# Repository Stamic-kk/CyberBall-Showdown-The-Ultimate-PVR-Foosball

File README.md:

# CyberBall-Showdown-The-Ultimate-PVR-Foosball
Purdue ECE Senior Design. A Player vs. Robot foosball table consists of ball tracking, trajectory computation, and motion control. A Jetson Nano serves as the central computation core, and a STM32F091 MCU is charge of all measurements and motion controls. \
See our website for any progress: https://engineering.purdue.edu/477grp9/ 
##
## Description
### Project Name: *Cyberball: The Ultimate PVR Foosball*
Foosball has been a popular form of entertainment for people of all ages. However, one constraint of the game is that it needs two people to play. It is not entertainment for an individual. Based on this issue, “Cyberball: PVR Foosball table” enables a player to play against an automated system, which consists of a high speed camera, three arrays of digital hall-effect sensors, two dedicated MCUs, and a set of servo motors.
The STM32 MCU leverages the data collected from hall-effect sensors to determine the location of the players on the rods. It then sends the location data to the Jetson Nano Developer Kit via UART protocol. The high speed camera captures the images of the foosball table and sends them to the Nano developer kit by USB protocol and Gstreamer pipeline with v4l2. Nano Developer Kit runs the Min-Max Location algorithm from the vision programming interface(VPI) to locate the ball, predict the trajectory using the extended Kalman filter, and make the decisions on moving rods, which the MCU processes into motor control signals. To achieve the detection purpose, the ball is colored uniquely. A sensitive pressure sensor is used to detect the goals.
The dynamics of the system contain two dimensions. For the rotational aspect, each rod has a high torque servo motor attached. These motors are continuously signaled on a constant frequency PWM, which allows the figures on the rods to maintain a swaying, kicking motion. For lateral movement, a structure of cables and pulleys transfers the angular momentum generated by a high speed servo motor to the linear motion of the rod. An MCU generates the PWM signal that activates the transistor channels between the servo and the DC source to make the servo rotate to the desired angle. This angular displacement pulls the cable attached to the rod, moving it horizontally.
An OLED display and a keypad connected to the STM32 act as the user interface where the users start/reset the game and view their goals. The OLED display communicates with the MCU with the SPI protocol and can be used to display the scores and user command options. The keypad (button array) communicates with the MCU through GPIO to send commands including start (power-on), re-start, and pause.
The power constraints are summarized as follows. The system needs a 6.8V DC for all 6 servo motors. MCUs and Jetson Nano will be powered by a 3.6V DC and a 5V=4A supply, respectively. The total power consumption is estimated to be 120W. The user simply plugs in the supplied 12V 30A AC/DC adapter. A set of buck converters and linear regulators will step down the main power source to voltages/currents required by the components.
##
### File Organization
> CAD 
>> Fusion 3D file for packaging design. 

>CyberBall - Configuration Code deployed on STM32F091 MCU (via Software Peripheral)
>> inc - include headers\
>> src - source files\
>> CyberBallConfig.cfg - run/debug configuration

> PCB - Kicad PCB design files
>> Librarys - Customized PCB layouts\
>> Hall_effect_sensors - Rod Position measurement board (x3)\
>> Power_Supply - Power supply board (commerical regulator modules needed)\
>> Senior Design - Main function board \
>> User_Interface - User Interface board with a screen on it. 

> nanoBrain - central control system runing on Jetson Nano.
>> cppSolution - CMAKE project for the workflow running on Jetson Nano\
>>> include - include headers\
>>> src - source files\
>>> uKal - helper submodule for the Kalman filter\

## Notes
**IMPORTANT**: <font color="red"> The VDD and GND pin are reversed on the pinout of connection for servos on the power supply board.</font>
+ VDD labled on the board should connect to GND pin on the servo.
+ GND labled on the board should connect to VDD pin on the servo.
+ No changes should be made for PWM control signals.

Note: disabled nvgetty for uart

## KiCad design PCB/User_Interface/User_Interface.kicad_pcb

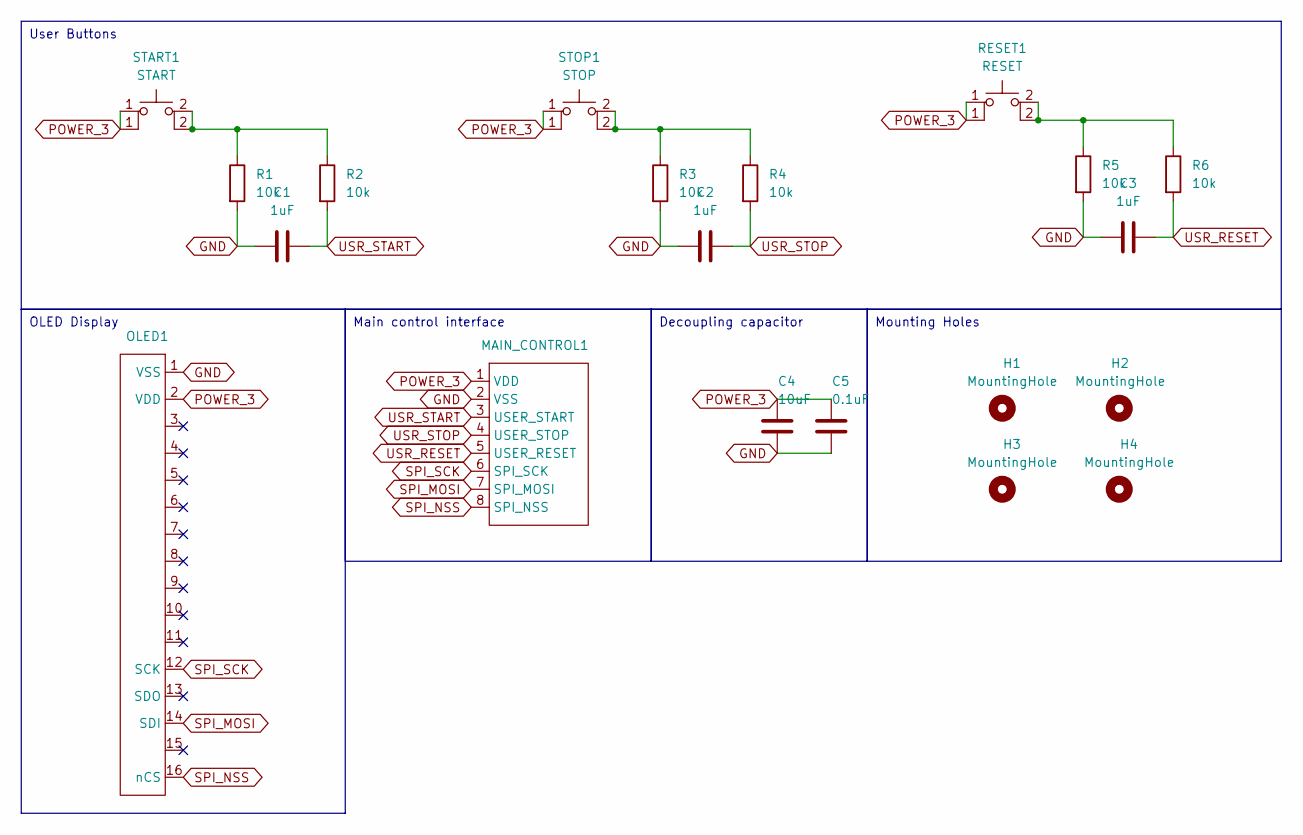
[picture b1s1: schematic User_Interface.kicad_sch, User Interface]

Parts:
C1, C2, C3: 1uF; C_1206_3216Metric_Pad1.33x1.80mm_HandSolder
C4: 10uF; C_1206_3216Metric_Pad1.33x1.80mm_HandSolder
C5: 0.1uF; C_1206_3216Metric_Pad1.33x1.80mm_HandSolder
H1, H2, H3, H4: MountingHole; MountingHole_4mm
MAIN_CONTROL1: PinSocket_1x08_P2.54mm_Vertical
OLED1: PinSocket_1x16_P2.54mm_Vertical
R1, R2, R3, R4, R5, R6: 10k; R_1206_3216Metric_Pad1.30x1.75mm_HandSolder
RESET1: RESET; SW_PUSH_6mm_H4.3mm
START1: START; SW_PUSH_6mm_H4.3mm
STOP1: STOP; SW_PUSH_6mm_H4.3mm

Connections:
GND: C1.1, C2.1, C3.1, C4.2, C5.2, MAIN_CONTROL1.2 (VSS), OLED1.1 (VSS), R1.2, R3.2, R5.2
unnamed: R5.1, R6.1, RESET1.2 (A)
unnamed: R1.1, R2.1, START1.2 (A)
unnamed: R3.1, R4.1, STOP1.2 (A)
POWER_3: C4.1, C5.1, MAIN_CONTROL1.1 (VDD), OLED1.2 (VDD), RESET1.1, START1.1, STOP1.1
SPI_MOSI: MAIN_CONTROL1.7 (SPI_MOSI), OLED1.14 (SDI)
SPI_NSS: MAIN_CONTROL1.8 (SPI_NSS), OLED1.16 (nCS)
SPI_SCK: MAIN_CONTROL1.6 (SPI_SCK), OLED1.12 (SCK)
USR_RESET: C3.2, MAIN_CONTROL1.5 (USER_RESET), R6.2
USR_START: C1.2, MAIN_CONTROL1.3 (USER_START), R2.2
USR_STOP: C2.2, MAIN_CONTROL1.4 (USER_STOP), R4.2

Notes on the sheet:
OLED Display
User Buttons
Main control interface
Decoupling capacitor
Mounting Holes

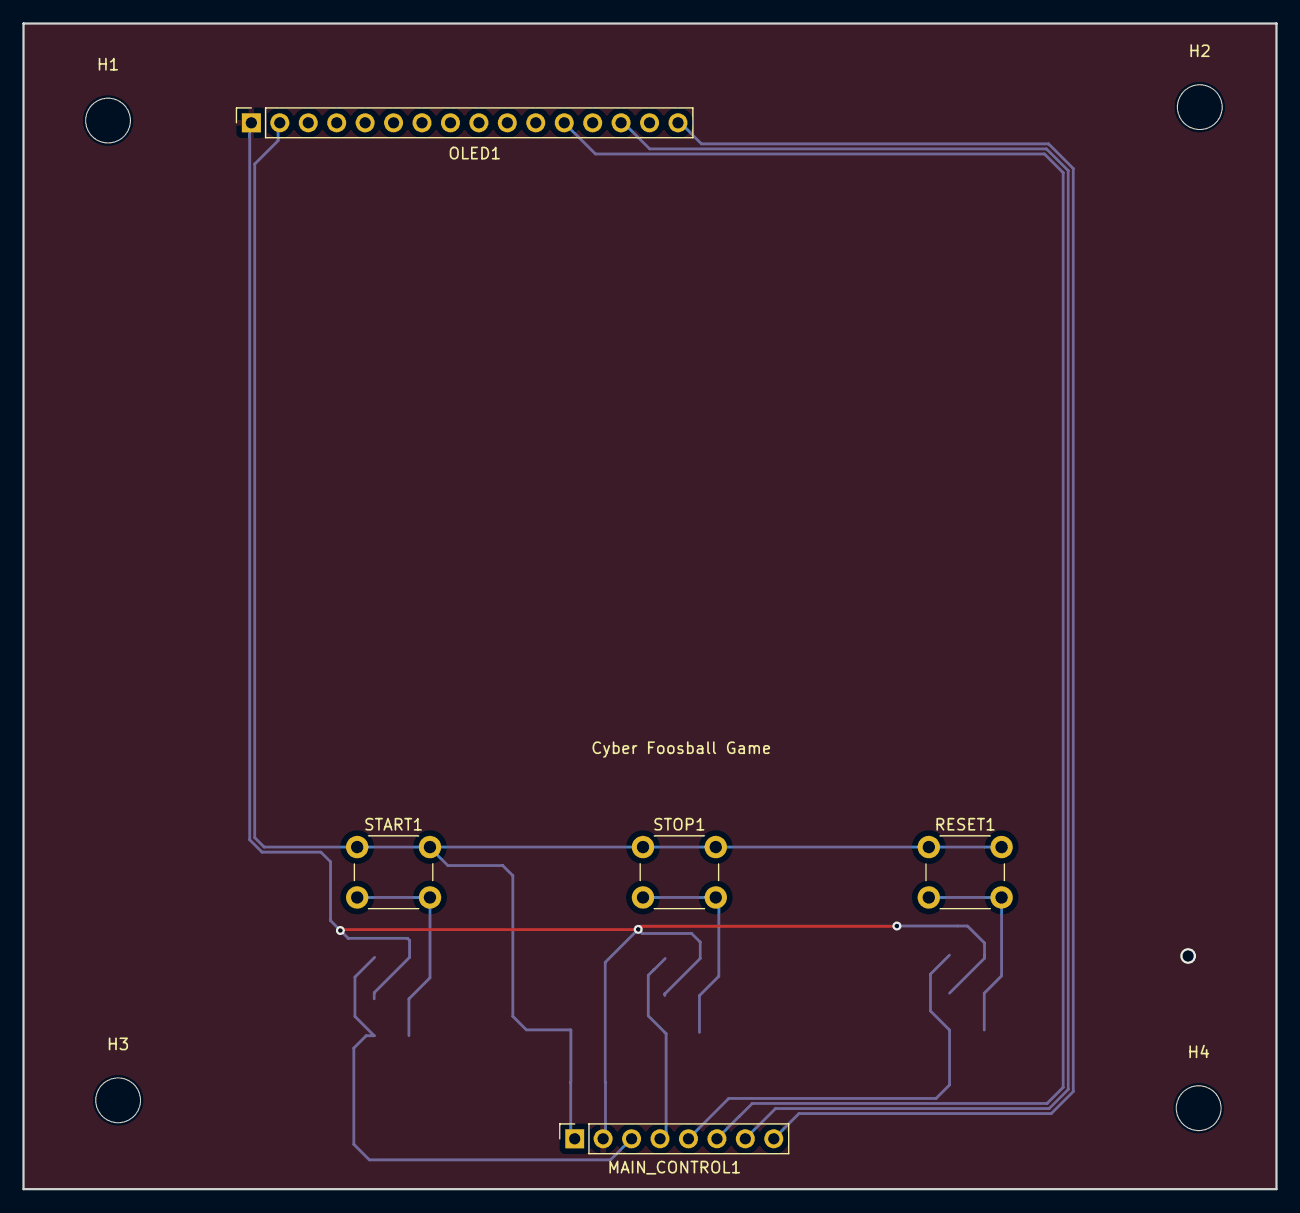
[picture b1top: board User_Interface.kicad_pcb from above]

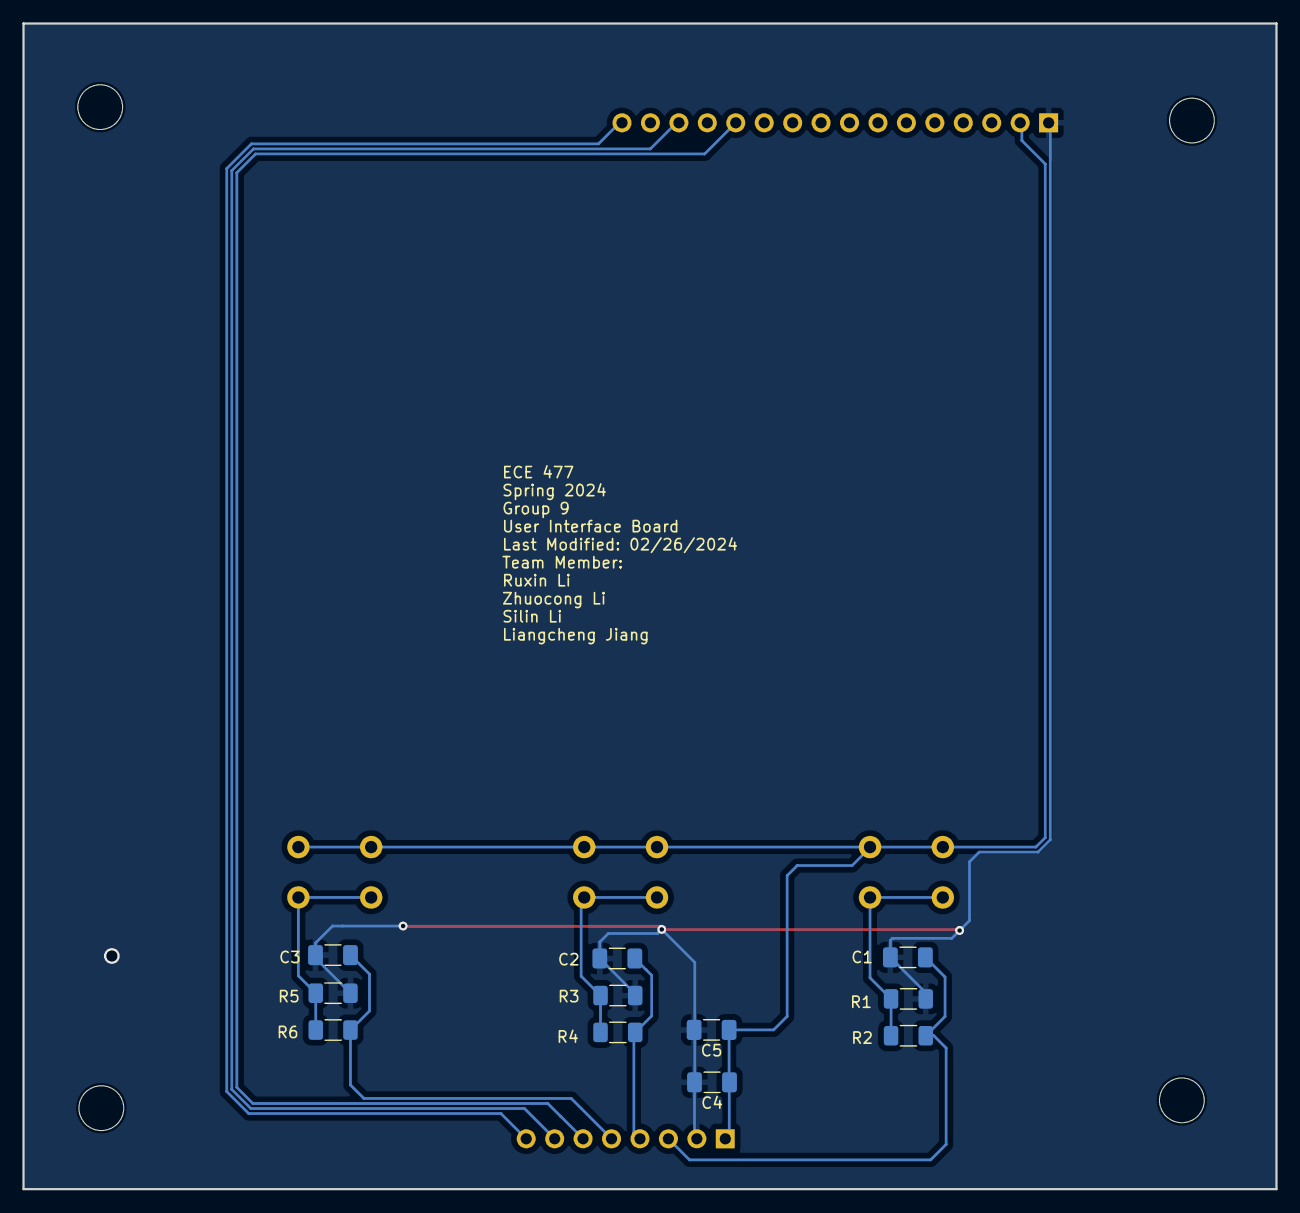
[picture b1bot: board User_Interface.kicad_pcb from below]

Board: 2 copper layers, 111.9 x 104.1 mm, 20 parts (11 on the bottom side), 11 nets.

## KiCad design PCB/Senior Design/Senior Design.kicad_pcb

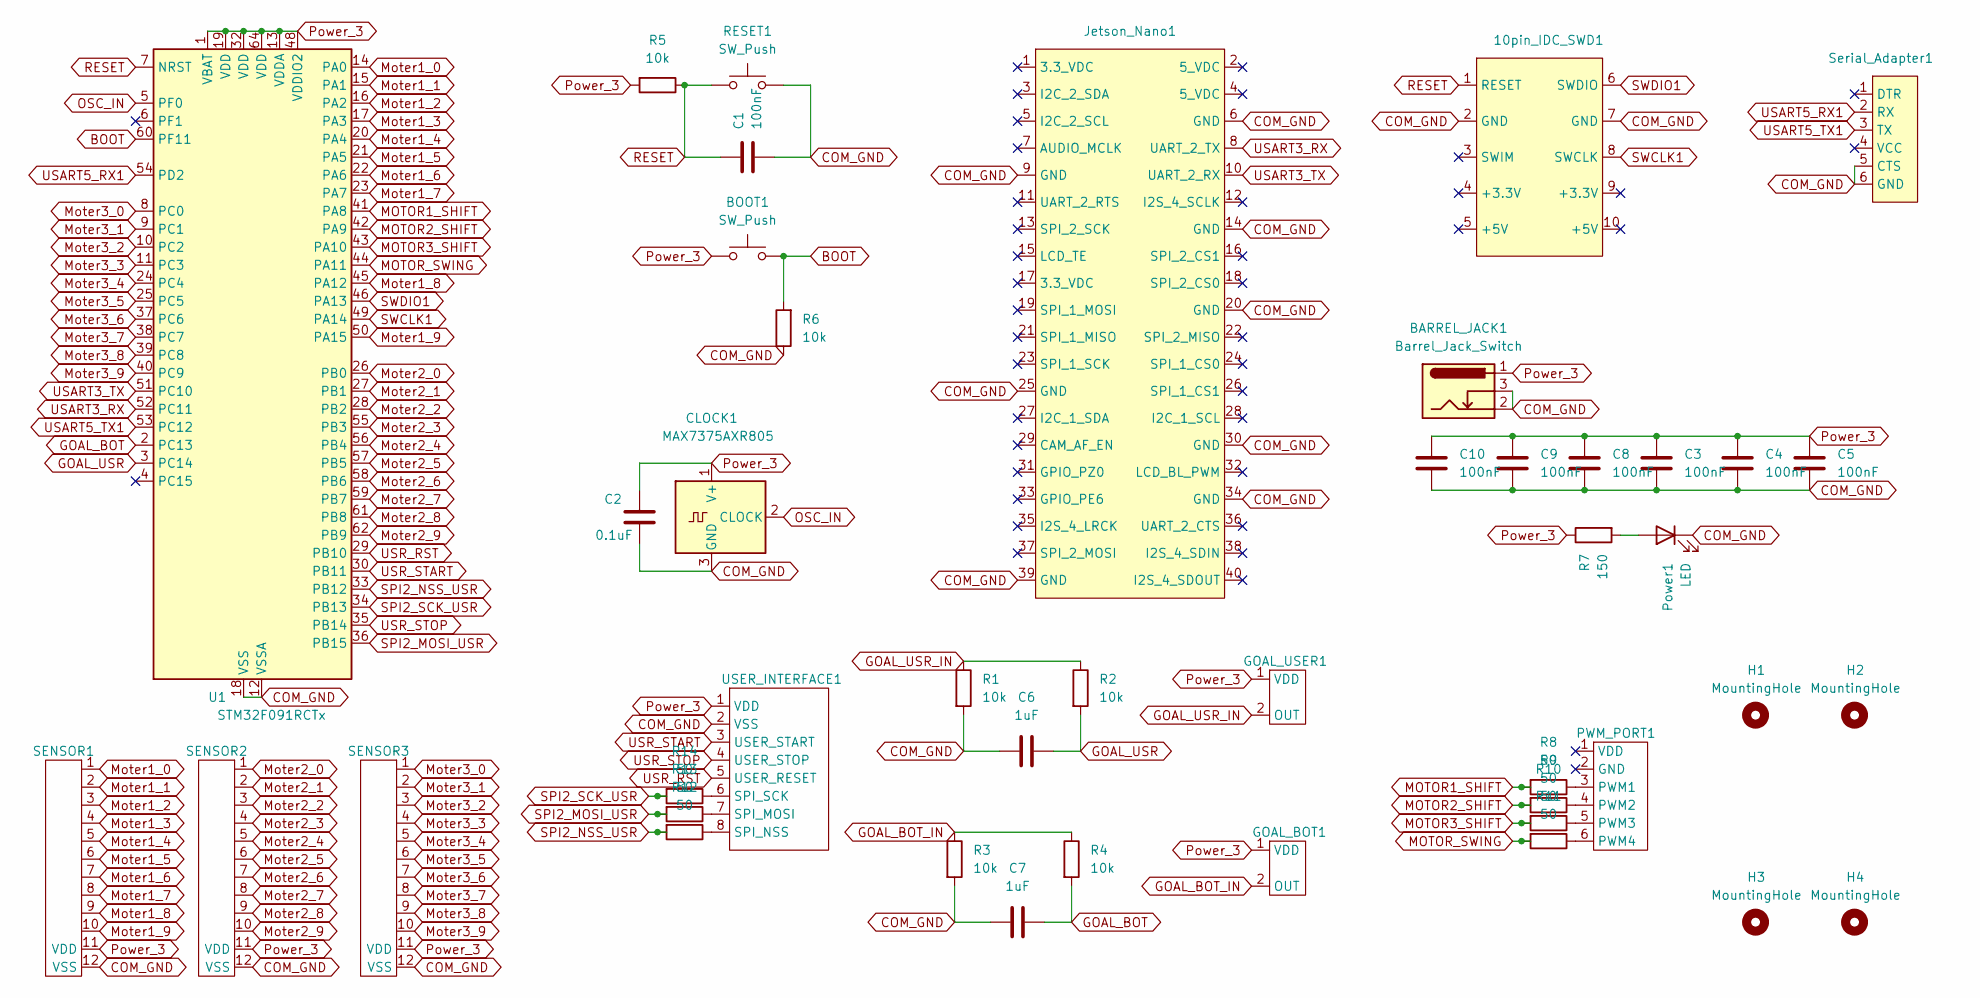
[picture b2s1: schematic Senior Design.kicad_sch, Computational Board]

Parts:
10pin_IDC_SWD1: IDC-Header_2x05_P2.54mm_Vertical_Modified
BARREL_JACK1: Barrel_Jack_Switch; BarrelJack_CUI_PJ-102AH_Horizontal
BOOT1: SW_Push; SW_PUSH_6mm_H4.3mm
C1, C3, C4, C5, C8, C9, C10: 100nF; C_1206_3216Metric_Pad1.33x1.80mm_HandSolder
C2: 0.1uF; C_1206_3216Metric_Pad1.33x1.80mm_HandSolder
C6, C7: 1uF; C_1206_3216Metric_Pad1.33x1.80mm_HandSolder
CLOCK1: MAX7375AXR805; SOT-323_SC-70
GOAL_BOT1: PinHeader_1x02_P2.54mm_Vertical
GOAL_USER1: PinHeader_1x02_P2.54mm_Vertical
H1, H2, H3, H4: MountingHole; MountingHole_4mm
Jetson_Nano1: PinHeader_2x20_P2.54mm_Vertical
PWM_PORT1: PinHeader_1x06_P2.54mm_Vertical
Power1: LED; LED_1206_3216Metric_Pad1.42x1.75mm_HandSolder
R1, R2, R3, R4, R5, R6: 10k; R_1206_3216Metric_Pad1.30x1.75mm_HandSolder
R7: 150; R_1206_3216Metric_Pad1.30x1.75mm_HandSolder
R8, R9, R10, R11, R12, R13, R14: 50; R_1206_3216Metric_Pad1.30x1.75mm_HandSolder
RESET1: SW_Push; SW_PUSH_6mm_H4.3mm
SENSOR1, SENSOR2, SENSOR3: PinHeader_1x12_P2.54mm_Vertical
Serial_Adapter1: PinSocket_1x06_P2.54mm_Vertical
U1: STM32F091RCTx; LQFP-64_10x10mm_P0.5mm
USER_INTERFACE1: PinHeader_1x08_P2.54mm_Vertical

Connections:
BOOT: BOOT1.2, R6.2, U1.60 (PF11)
COM_GND: 10pin_IDC_SWD1.2 (GND), 10pin_IDC_SWD1.7 (GND), BARREL_JACK1.2, BARREL_JACK1.3, C1.2, C2.2, C3.2, C4.2, C5.2, C6.1, C7.1, C8.2, C9.2, C10.2, CLOCK1.3 (GND), Jetson_Nano1.6 (GND), Jetson_Nano1.9 (GND), Jetson_Nano1.14 (GND), Jetson_Nano1.20 (GND), Jetson_Nano1.25 (GND), Jetson_Nano1.30 (GND), Jetson_Nano1.34 (GND), Jetson_Nano1.39 (GND), Power1.1 (K), R1.2, R3.2, R6.1, RESET1.2, SENSOR1.12 (VSS), SENSOR2.12 (VSS), SENSOR3.12 (VSS), Serial_Adapter1.5 (CTS), Serial_Adapter1.6 (GND), U1.12 (VSSA), U1.18 (VSS), U1.31 (VSS), U1.47 (VSS), U1.63 (VSS), USER_INTERFACE1.2 (VSS)
GOAL_BOT: C7.2, R4.2, U1.2 (PC13)
GOAL_BOT_IN: GOAL_BOT1.2 (OUT), R3.1, R4.1
GOAL_USR: C6.2, R2.2, U1.3 (PC14)
GOAL_USR_IN: GOAL_USER1.2 (OUT), R1.1, R2.1
MOTOR1_SHIFT: R8.2, U1.41 (PA8)
MOTOR2_SHIFT: R9.2, U1.42 (PA9)
MOTOR3_SHIFT: R10.2, U1.43 (PA10)
MOTOR_SWING: R11.2, U1.44 (PA11)
Moter1_0: SENSOR1.1, U1.14 (PA0)
Moter1_1: SENSOR1.2, U1.15 (PA1)
Moter1_2: SENSOR1.3, U1.16 (PA2)
Moter1_3: SENSOR1.4, U1.17 (PA3)
Moter1_4: SENSOR1.5, U1.20 (PA4)
Moter1_5: SENSOR1.6, U1.21 (PA5)
Moter1_6: SENSOR1.7, U1.22 (PA6)
Moter1_7: SENSOR1.8, U1.23 (PA7)
Moter1_8: SENSOR1.9, U1.45 (PA12)
Moter1_9: SENSOR1.10, U1.50 (PA15)
Moter2_0: SENSOR2.1, U1.26 (PB0)
Moter2_1: SENSOR2.2, U1.27 (PB1)
Moter2_2: SENSOR2.3, U1.28 (PB2)
Moter2_3: SENSOR2.4, U1.55 (PB3)
Moter2_4: SENSOR2.5, U1.56 (PB4)
Moter2_5: SENSOR2.6, U1.57 (PB5)
Moter2_6: SENSOR2.7, U1.58 (PB6)
Moter2_7: SENSOR2.8, U1.59 (PB7)
Moter2_8: SENSOR2.9, U1.61 (PB8)
Moter2_9: SENSOR2.10, U1.62 (PB9)
Moter3_0: SENSOR3.1, U1.8 (PC0)
Moter3_1: SENSOR3.2, U1.9 (PC1)
Moter3_2: SENSOR3.3, U1.10 (PC2)
Moter3_3: SENSOR3.4, U1.11 (PC3)
Moter3_4: SENSOR3.5, U1.24 (PC4)
Moter3_5: SENSOR3.6, U1.25 (PC5)
Moter3_6: SENSOR3.7, U1.37 (PC6)
Moter3_7: SENSOR3.8, U1.38 (PC7)
Moter3_8: SENSOR3.9, U1.39 (PC8)
Moter3_9: SENSOR3.10, U1.40 (PC9)
unnamed: PWM_PORT1.3 (PWM1), R8.1
unnamed: PWM_PORT1.4 (PWM2), R9.1
unnamed: PWM_PORT1.5 (PWM3), R10.1
unnamed: PWM_PORT1.6 (PWM4), R11.1
unnamed: Power1.2 (A), R7.2
unnamed: R13.1, USER_INTERFACE1.7 (SPI_MOSI)
unnamed: R12.1, USER_INTERFACE1.8 (SPI_NSS)
unnamed: R14.1, USER_INTERFACE1.6 (SPI_SCK)
OSC_IN: CLOCK1.2 (CLOCK), U1.5 (PF0)
Power_3: BARREL_JACK1.1, BOOT1.1, C2.1, C3.1, C4.1, C5.1, C8.1, C9.1, C10.1, CLOCK1.1 (V+), GOAL_BOT1.1 (VDD), GOAL_USER1.1 (VDD), R5.2, R7.1, SENSOR1.11 (VDD), SENSOR2.11 (VDD), SENSOR3.11 (VDD), U1.1 (VBAT), U1.13 (VDDA), U1.19 (VDD), U1.32 (VDD), U1.48 (VDDIO2), U1.64 (VDD), USER_INTERFACE1.1 (VDD)
RESET: 10pin_IDC_SWD1.1 (RESET), C1.1, R5.1, RESET1.1, U1.7 (NRST)
SPI2_MOSI_USR: R13.2, U1.36 (PB15)
SPI2_NSS_USR: R12.2, U1.33 (PB12)
SPI2_SCK_USR: R14.2, U1.34 (PB13)
SWCLK1: 10pin_IDC_SWD1.8 (SWCLK), U1.49 (PA14)
SWDIO1: 10pin_IDC_SWD1.6 (SWDIO), U1.46 (PA13)
USART3_RX: Jetson_Nano1.8 (UART_2_TX), U1.52 (PC11)
USART3_TX: Jetson_Nano1.10 (UART_2_RX), U1.51 (PC10)
USART5_RX1: Serial_Adapter1.2 (RX), U1.54 (PD2)
USART5_TX1: Serial_Adapter1.3 (TX), U1.53 (PC12)
USR_RST: U1.29 (PB10), USER_INTERFACE1.5 (USER_RESET)
USR_START: U1.30 (PB11), USER_INTERFACE1.3 (USER_START)
USR_STOP: U1.35 (PB14), USER_INTERFACE1.4 (USER_STOP)

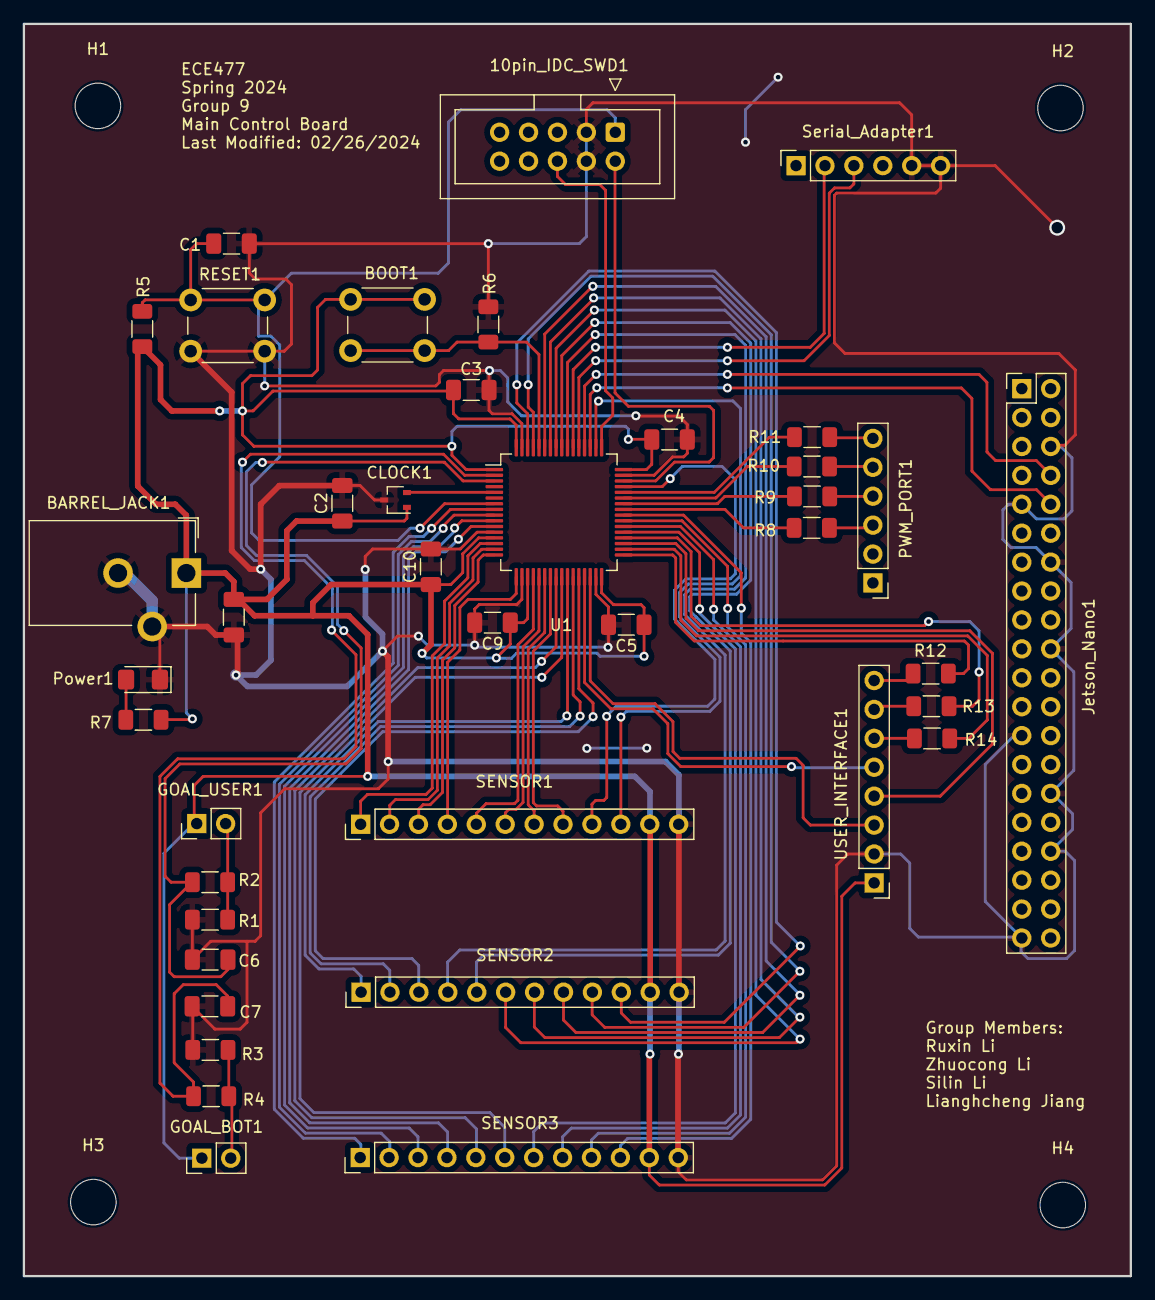
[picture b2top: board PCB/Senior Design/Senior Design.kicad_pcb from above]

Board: 2 copper layers, 97.2 x 110.0 mm, 44 parts (0 on the bottom side), 63 nets.

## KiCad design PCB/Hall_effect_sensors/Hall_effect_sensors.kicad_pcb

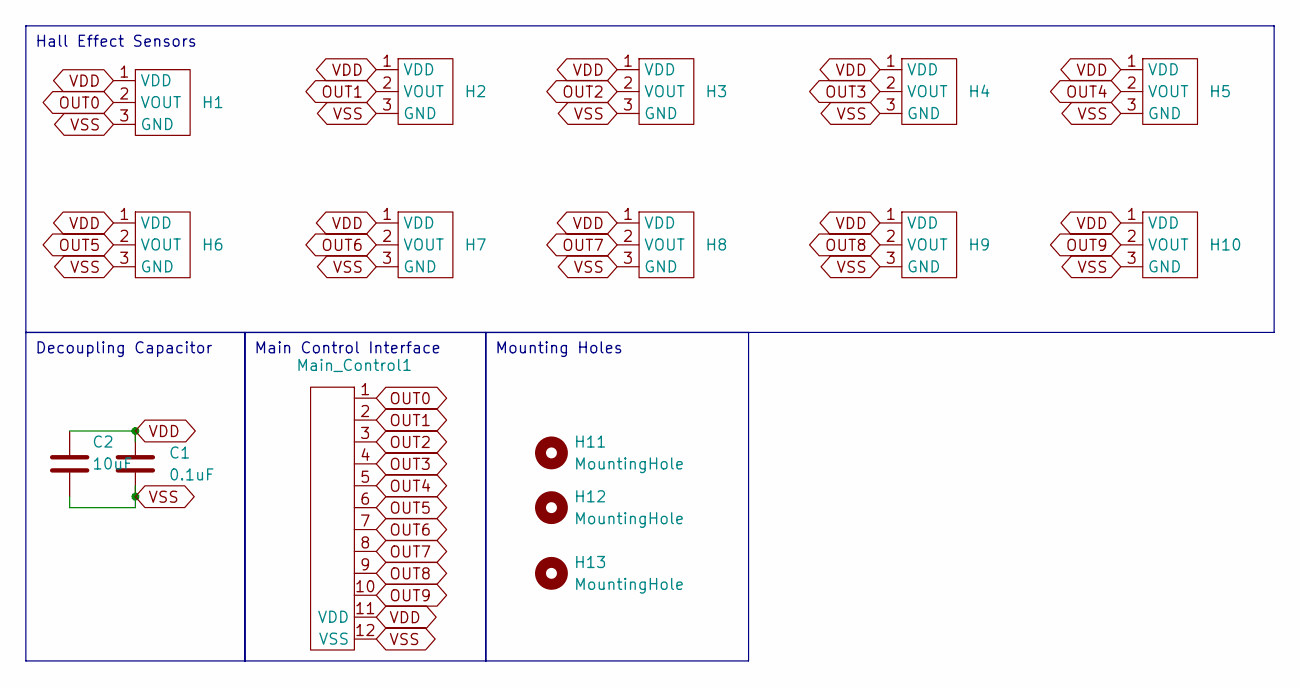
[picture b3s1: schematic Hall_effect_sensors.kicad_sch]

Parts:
C1: 0.1uF; C_1206_3216Metric_Pad1.33x1.80mm_HandSolder
C2: 10uF; C_1206_3216Metric_Pad1.33x1.80mm_HandSolder
H1, H2, H3, H4, H5, H6, H7, H8, H9, H10: SOT-23-3
H11, H12: MountingHole; MountingHole_4mm
H13: MountingHole; MountingHole_2mm
Main_Control1: Sensor Port

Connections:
OUT0: H1.2 (VOUT), Main_Control1.1
OUT1: H2.2 (VOUT), Main_Control1.2
OUT2: H3.2 (VOUT), Main_Control1.3
OUT3: H4.2 (VOUT), Main_Control1.4
OUT4: H5.2 (VOUT), Main_Control1.5
OUT5: H6.2 (VOUT), Main_Control1.6
OUT6: H7.2 (VOUT), Main_Control1.7
OUT7: H8.2 (VOUT), Main_Control1.8
OUT8: H9.2 (VOUT), Main_Control1.9
OUT9: H10.2 (VOUT), Main_Control1.10
VDD: C1.1, C2.1, H1.1 (VDD), H2.1 (VDD), H3.1 (VDD), H4.1 (VDD), H5.1 (VDD), H6.1 (VDD), H7.1 (VDD), H8.1 (VDD), H9.1 (VDD), H10.1 (VDD), Main_Control1.11 (VDD)
VSS: C1.2, C2.2, H1.3 (GND), H2.3 (GND), H3.3 (GND), H4.3 (GND), H5.3 (GND), H6.3 (GND), H7.3 (GND), H8.3 (GND), H9.3 (GND), H10.3 (GND), Main_Control1.12 (VSS)

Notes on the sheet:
Mounting Holes
Hall Effect Sensors
Main Control Interface
Decoupling Capacitor

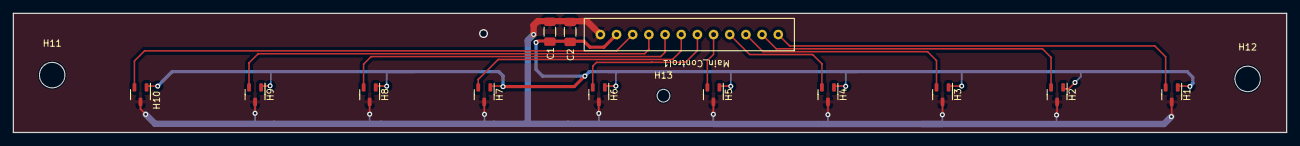
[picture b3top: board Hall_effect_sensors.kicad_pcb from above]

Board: 2 copper layers, 200.0 x 18.7 mm, 16 parts (0 on the bottom side), 12 nets.

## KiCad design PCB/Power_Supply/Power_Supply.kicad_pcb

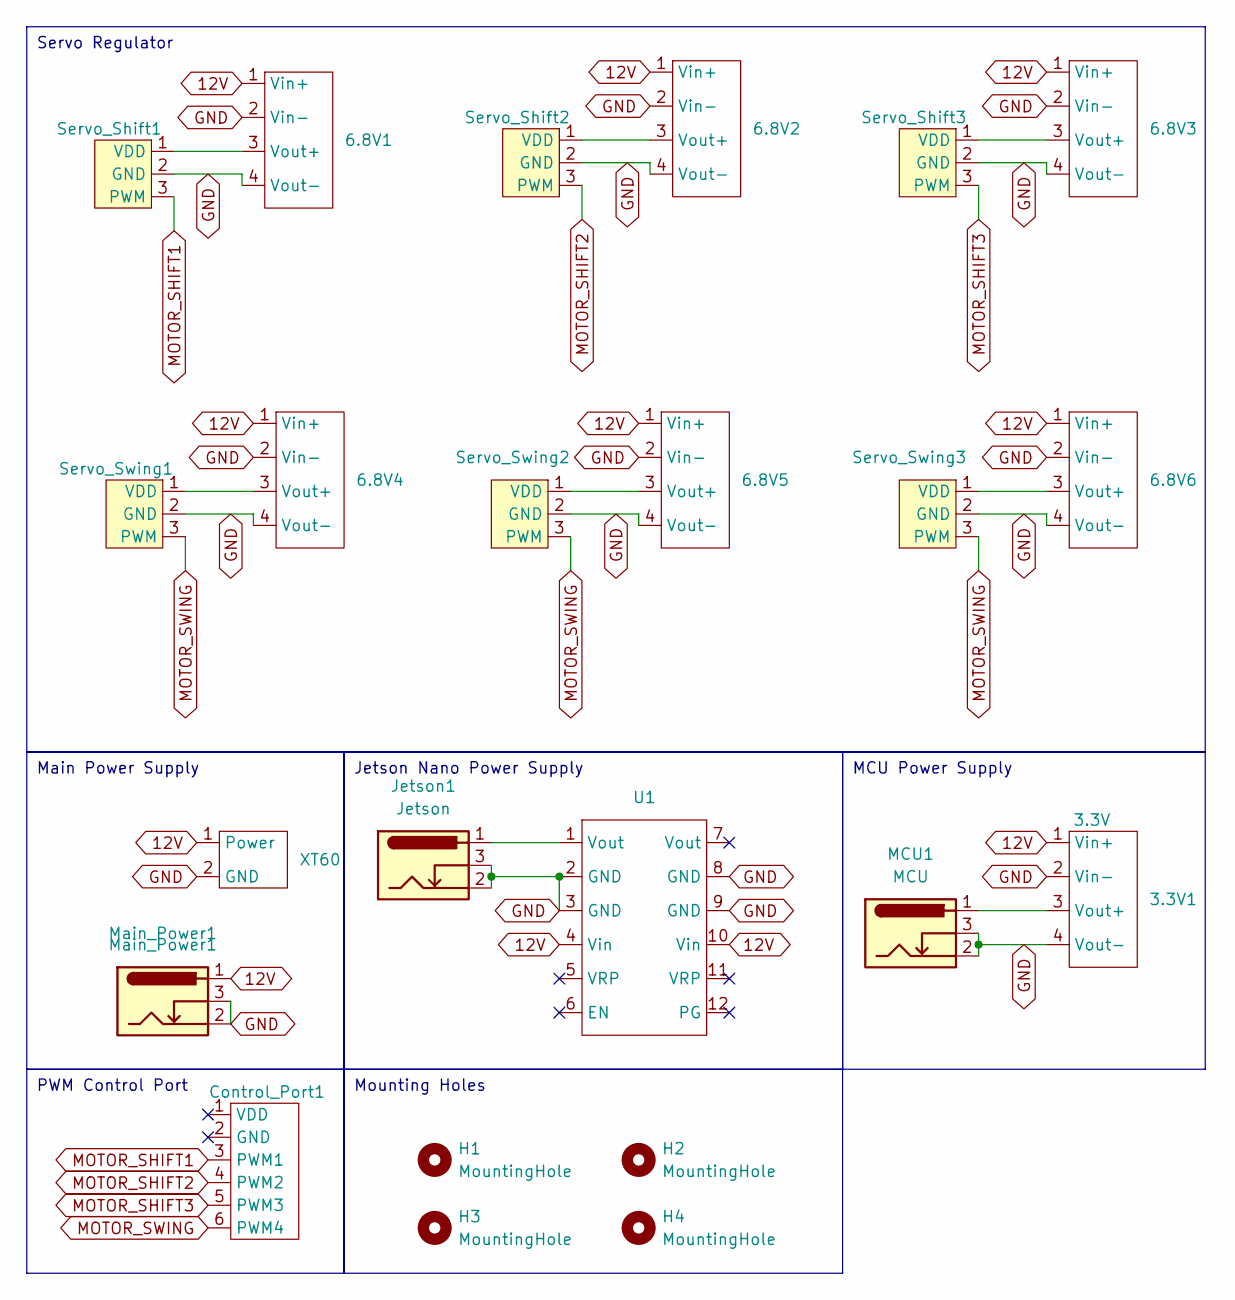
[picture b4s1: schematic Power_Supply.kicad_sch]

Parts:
3.3V1: 3.3V; LM2596
6.8V1, 6.8V2, 6.8V3, 6.8V4, 6.8V5, 6.8V6: LM2596
Control_Port1: PinHeader_1x06_P2.54mm_Vertical
H1, H2, H3, H4: MountingHole; MountingHole_2.5mm
Jetson1: Jetson; BarrelJack_CUI_PJ-102AH_Horizontal
MCU1: MCU; BarrelJack_CUI_PJ-102AH_Horizontal
Main_Power1: Main_Power1; BarrelJack_CUI_PJ-102AH_Horizontal
Servo_Shift1, Servo_Shift2, Servo_Shift3: PinHeader_1x03_P2.54mm_Vertical
Servo_Swing1, Servo_Swing2, Servo_Swing3: PinHeader_1x03_P2.54mm_Vertical
U1: PinHeader_2x06_P2.54mm_Vertical
XT60: AMASS_XT60-M_1x02_P7.20mm_Vertical

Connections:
12V: 3.3V1.1 (Vin+), 6.8V1.1 (Vin+), 6.8V2.1 (Vin+), 6.8V3.1 (Vin+), 6.8V4.1 (Vin+), 6.8V5.1 (Vin+), 6.8V6.1 (Vin+), Main_Power1.1, U1.4 (Vin), U1.10 (Vin), XT60.1 (Power)
GND: 3.3V1.2 (Vin-), 3.3V1.4 (Vout-), 6.8V1.2 (Vin-), 6.8V1.4 (Vout-), 6.8V2.2 (Vin-), 6.8V2.4 (Vout-), 6.8V3.2 (Vin-), 6.8V3.4 (Vout-), 6.8V4.2 (Vin-), 6.8V4.4 (Vout-), 6.8V5.2 (Vin-), 6.8V5.4 (Vout-), 6.8V6.2 (Vin-), 6.8V6.4 (Vout-), Jetson1.2, Jetson1.3, MCU1.2, MCU1.3, Main_Power1.2, Main_Power1.3, Servo_Shift1.2 (GND), Servo_Shift2.2 (GND), Servo_Shift3.2 (GND), Servo_Swing1.2 (GND), Servo_Swing2.2 (GND), Servo_Swing3.2 (GND), U1.2 (GND), U1.3 (GND), U1.8 (GND), U1.9 (GND), XT60.2 (GND)
MOTOR_SHIFT1: Control_Port1.3 (PWM1), Servo_Shift1.3 (PWM)
MOTOR_SHIFT2: Control_Port1.4 (PWM2), Servo_Shift2.3 (PWM)
MOTOR_SHIFT3: Control_Port1.5 (PWM3), Servo_Shift3.3 (PWM)
MOTOR_SWING: Control_Port1.6 (PWM4), Servo_Swing1.3 (PWM), Servo_Swing2.3 (PWM), Servo_Swing3.3 (PWM)
unnamed: 3.3V1.3 (Vout+), MCU1.1
unnamed: 6.8V1.3 (Vout+), Servo_Shift1.1 (VDD)
unnamed: 6.8V2.3 (Vout+), Servo_Shift2.1 (VDD)
unnamed: 6.8V3.3 (Vout+), Servo_Shift3.1 (VDD)
unnamed: 6.8V4.3 (Vout+), Servo_Swing1.1 (VDD)
unnamed: 6.8V5.3 (Vout+), Servo_Swing2.1 (VDD)
unnamed: 6.8V6.3 (Vout+), Servo_Swing3.1 (VDD)
unnamed: Jetson1.1, U1.1 (Vout)

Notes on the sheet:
Main Power Supply
PWM Control Port
Jetson Nano Power Supply
Servo Regulator
MCU Power Supply
Mounting Holes

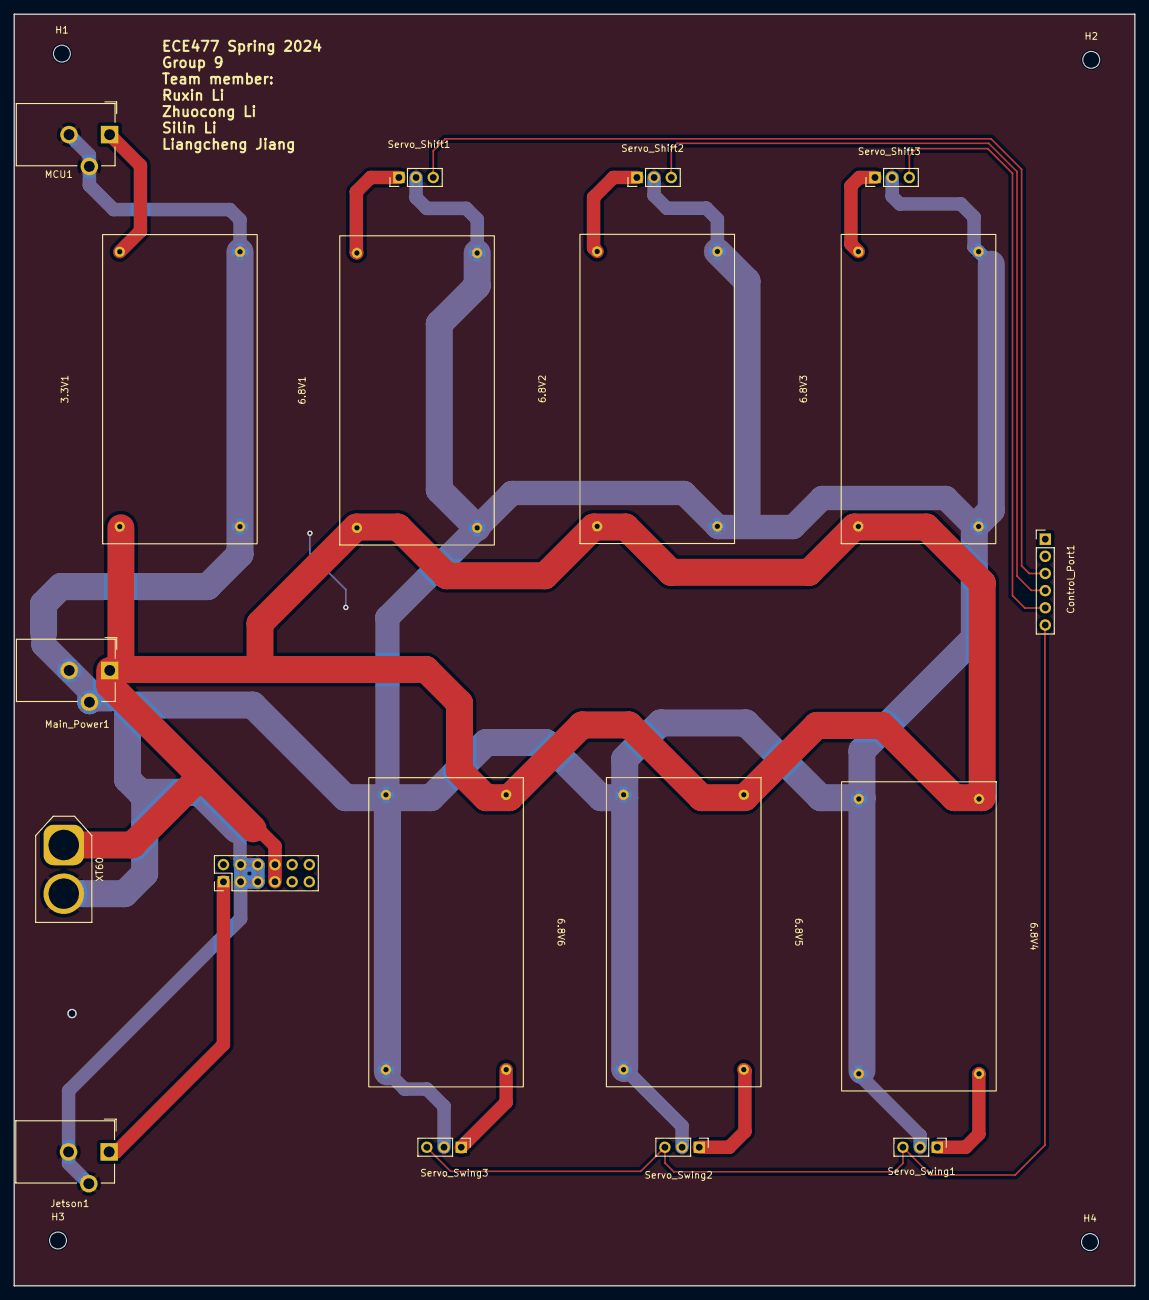
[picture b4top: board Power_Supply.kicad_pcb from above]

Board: 2 copper layers, 165.7 x 188.0 mm, 23 parts (0 on the bottom side), 14 nets.
